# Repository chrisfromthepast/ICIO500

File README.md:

# ICIO500

Transformerless line-in and line-out prototyping platform for the **API VPR-500** 500-series modular rack (`1.500" × 5.250"`), powered by a Daisy Seed DSP carrier card, a vertical rotary-encoder daughtercard, and a modular **0.8 mm Satellite PCB + Swappable Front Panel** faceplate stackup.

---

## Quick Start: View the Full 3D Module in KiCad
1. Open either full 3D assembly in KiCad 10 PCB Editor:
   - **Walnut / Stained Wood Horizontal Slots + Diffuser Film:** [`kicad/icio500_satellite_wood_3d.kicad_pcb`](kicad/icio500_satellite_wood_3d.kicad_pcb)
   - **Dead-Front Smoked Acrylic:** [`kicad/icio500_satellite_acrylic_3d.kicad_pcb`](kicad/icio500_satellite_acrylic_3d.kicad_pcb)
2. Press **`Alt + 3`** to orbit the full stackup (`Carrier PCB` + `Encoder Daughtercard` + inset `0.8 mm Satellite PCB` + `Front Panel` + `Capstan Knob`).
3. Browse pre-rendered views directly in [`renders/`](renders/).

---

## Repository Structure

| Folder | Contents |
| :--- | :--- |
| [`kicad/`](kicad/) | Active KiCad PCBs, schematics (`october_surprise.kicad_sch` + `october_surprise.kicad_pcb`), local footprint libraries (`Cards.pretty/`, `custom.pretty/`), `spice_models/`, `3d_models/`, and 3D assemblies. |
| [`fabrication/`](fabrication/) | Ready-to-upload manufacturing packages separated into `in_production/` (locked) and `satellite_faceplate/` (active). |
| [`firmware/`](firmware/) | Daisy Seed C++ DSP projects (`roomove/`, `cloudseed/`, `daisyverb/`, `covol/`, `funbox_reverbs/`) and shared pinout header `common/icio500_hw.h`. |
| [`scripts/`](scripts/) | Python CAD, KiCad schematic/PCB builder, in-KiCad `ngspice` verification, BOM export, DRC, and fab-export scripts. |
| [`renders/`](renders/) | Verified high-resolution KiCad 3D renders of the modular satellite assemblies and rear PCB layout. |
| [`docs/`](docs/) | API VPR-500 mechanical spec (`api_vpr_500_spec.pdf`), raw manufacturer PDFs (`datasheets/`), `october_surprise_schematic.pdf`, draft BOM, and `ngspice` verification plots. |
| [`archive/`](archive/) | Archived Rev-1 carrier reference (`archive/rev1_bad_carrier/`), preserved strictly as mechanical salvage reference. |

---

## Board & Fabrication Status

| Subsystem | Design Files | Manufacturing Package | Status |
| :--- | :--- | :--- | :--- |
| **VPR-500 Carrier PCB (`October Surprise` Rev 2)** | `kicad/october_surprise.kicad_sch`, `kicad/october_surprise.kicad_pcb` | *(Pre-routing — Subcircuit #1 `POWER` verified)* | **IN DESIGN (Schematic-First + In-KiCad `ngspice`)** |
| **Encoder Daughtercard** | `kicad/encoder_board.kicad_pcb` | [`fabrication/in_production/jlcpcb_encoder/`](fabrication/in_production/jlcpcb_encoder/) | **IN PRODUCTION (Locked)** |
| **Capstan Vernier Knob** | [`scripts/generate_capstan_v2_knob.py`](scripts/generate_capstan_v2_knob.py) | [`fabrication/in_production/jlc3dp_knob_v2/`](fabrication/in_production/jlc3dp_knob_v2/) | **IN PRODUCTION (Locked)** |
| **0.8 mm Satellite Active PCB** | `kicad/faceplate_satellite.kicad_pcb`, `kicad/faceplate_logic.kicad_sch` | [`fabrication/satellite_faceplate/jlcpcb_satellite_pcb/`](fabrication/satellite_faceplate/jlcpcb_satellite_pcb/) | **ACTIVE (0.8 mm 2L FR4, Matte Black)** |
| **Swappable Front Panels** | [`scripts/generate_sendcutsend_faceplates.py`](scripts/generate_sendcutsend_faceplates.py) | [`fabrication/satellite_faceplate/sendcutsend_panels/`](fabrication/satellite_faceplate/sendcutsend_panels/) | **ACTIVE (SendCutSend/Ponoko DXFs + STEP + Preview)** |

---

## Modular Satellite Stackup Notes
- **Hidden Satellite Inset:** `faceplate_satellite.kicad_pcb` (`35.10 × 113.35 mm`, `0.8 mm` 2-layer FR4, recommend **Matte Black** soldermask) sits inset `1.50 mm` left/right and `10.00 mm` top/bottom behind the `38.10 × 133.35 mm` front panel so only the single-layer wood/acrylic panel meets the 500-series rack rails.
- **No Blind Slots Required:** Reverse-mount gull-wing LEDs (`D1..D16`) mount on `B.Cu` over standard `1.92 × 1.68 mm` full NPTH oval slots.
- **Front Panel Diffuser Options:**
  - *Horizontal-Slot Wood (`0.125"` / `3.175 mm`):* `10×` `7.20 × 2.40 mm` horizontal stadium slots (`8.00 mm` pitch) + `6× Ø2.40 mm` knob-ring ports, backed by a flat sheet of translucent milky-white diffusion tape/film (e.g., `3M 3635-70` or Roscolux Tough Frost) sandwiched between the Satellite PCB and Wood.
  - *Dead-Front Smoked Acrylic (`0.118"` / `3.000 mm`):* Zero LED cutouts — all `16` LEDs shine directly through the translucent smoked panel.
- **Mechanical Mating:** `BR1/BR2` (`WP-SMRA-M3`), `J1` (`2x10` header), top `2× M2.5` screws, and the `PEC11R` `M7` bushing mate directly with the locked Carrier and Encoder PCBs. With `3.00–3.18 mm` front panels, place a `~1.8–2.0 mm` spacer inside the in-production Capstan Knob bore to maintain the `1.00 mm` click clearance.

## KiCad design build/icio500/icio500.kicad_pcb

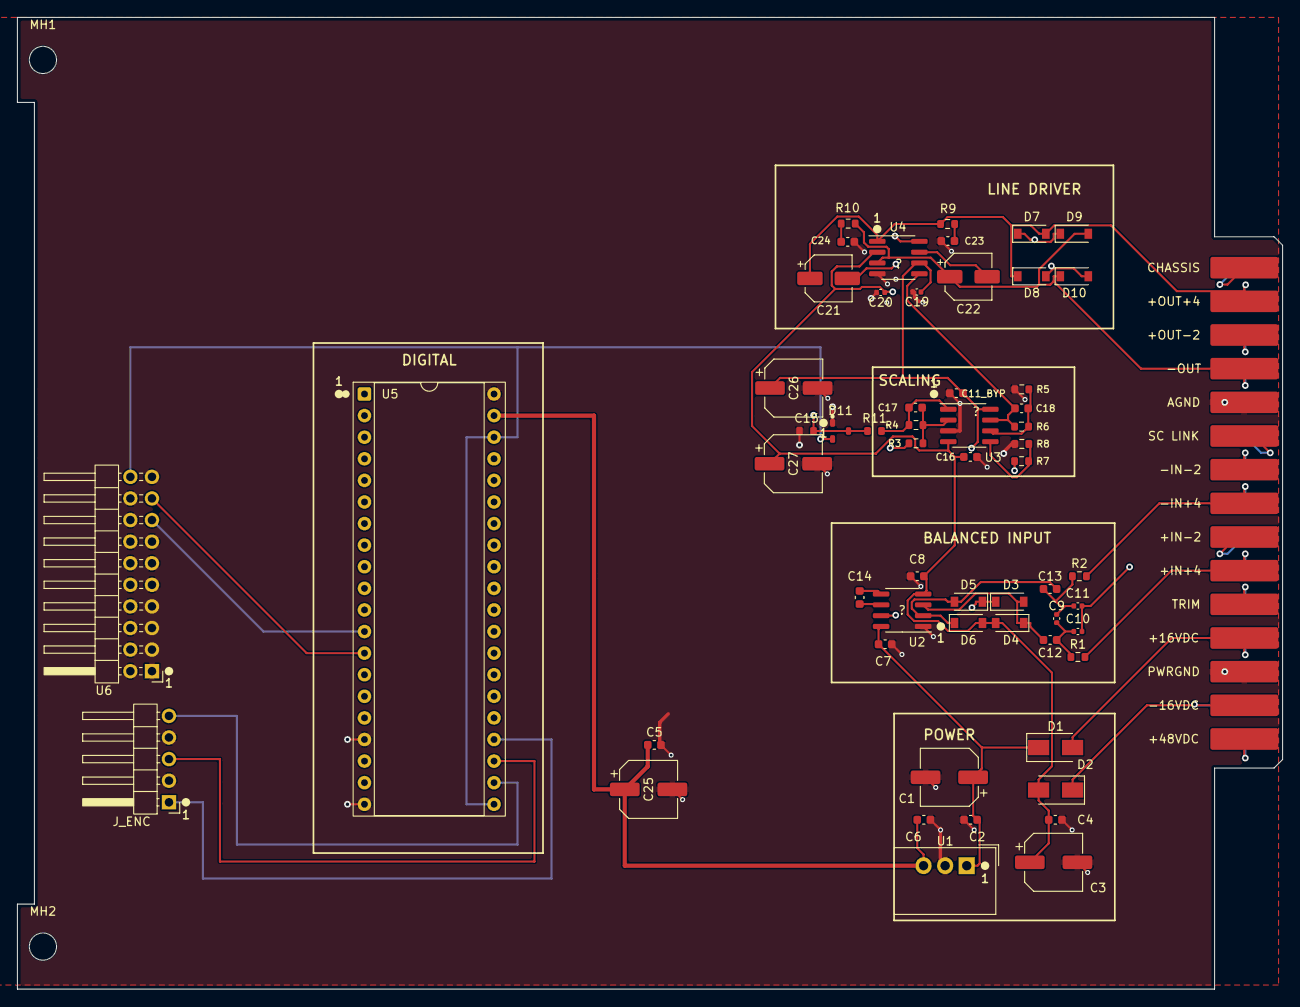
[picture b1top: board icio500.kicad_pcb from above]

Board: 4 copper layers, 148.8 x 114.3 mm, 60 parts (0 on the bottom side), 35 nets.

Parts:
C1, C3, C25, C26, C27: ?; CP_Elec_6.3x5.4
C2, C4, C5, C6, C7, C8, C11_BYP, C12, C13, C14, C16, C17, C18, C23, C24: C0603
C9, C10, C11, C19, C20: C0402
C15: 100pF; C0603
C21, C22: ?; CP_Elec_5x5.4
D1, D2: ?; D_SMA
D3, D4, D5, D6, D7, D8, D9, D10: ?; D_SOD-123
D11: BAT54S; SOT-23
J1: ?; EDA_306
J_ENC: Conn_01x05_Encoder; PinHeader_1x05_P2.54mm_Horizontal
MH1, MH2: MountingHole_3.2mm_M3
R1, R2, R3, R4, R5, R6, R7, R8, R9, R10: R0603
R11: 1k; R0603
U1: TSR 1-2450; Converter_DCDC_TRACO_TSR-1_THT
U2, U3, U4: ?; SOIC-8_3.9x4.9mm_P1.27mm
U5: ?; DIP-40_W15.24mm_Socket
U6: 2541WR-2x10P; PinHeader_2x10_P2.54mm_Horizontal

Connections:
+3.3V: D11.2, U5.21, U5.38, U6.20
audio_in_from_daisy_plus: R7.1, U5.18
audio_out: R3.1, U2.7
audio_out_to_1646: C18.1, R6.1, U3.7, U4.5
chassis_gnd: C10.2, C11.2, J1.1
cm: C14.1, U2.6
d14: J_ENC.5, U5.22
daisy_5v_power: C5.1, C6.1, C25.1, U1.3, U5.39
daisy_audio_in: C15.1, D11.3, R11.2, U5.16
driver.r_zobel_minus-vcc: C24.1, R10.2
driver.r_zobel_plus-vcc: C23.1, R9.2
gnd: C1.2, C2.2, C3.2, C4.2, C5.2, C6.2, C7.2, C8.2, C11_BYP.2, C15.2, C16.2, C19.2, C20.2, C23.2, C24.2, C25.2, C26.2, C27.2, D11.1, J1.5, J1.13, J_ENC.2, J_ENC.4, R5.1, R8.1, U1.2, U2.1, U3.3, U4.4, U5.17, U5.20, U5.40, U6.1, U6.2, U6.3, U6.4, U6.5, U6.6, U6.7, U6.8, U6.9, U6.10, U6.11, U6.12, U6.13, U6.14, U6.16, U6.18, U6.19
gpio_enc_b: J_ENC.3, U5.23
gpio_enc_sw: J_ENC.1, U5.24
i2c1_scl: U5.12, U6.15
i2c1_sda: U5.13, U6.17
in_minus: C13.2, D5.2, D6.1, U2.2
in_minus_1: C17.2, R3.2, R4.2, U3.2
in_minus_2: C18.2, R5.2, R6.2, U3.6
in_minus_4dbu: J1.8, R2.1
in_plus: C12.2, D3.2, D4.1, U2.3
in_plus_2: R7.2, R8.2, U3.5
in_plus_4dbu: J1.10, R1.1
out_minus: C22.1, D9.2, D10.1, J1.4, R10.1, U4.3
out_plus_4dbu: C21.1, D7.2, D8.1, J1.2, R9.1, U4.1
receiver.r_rf_minus-vcc: C9.2, C11.1, C13.1, R2.2
receiver.r_rf_plus-vcc: C9.1, C10.1, C12.1, R1.2
sense_minus: C22.2, U4.7
sense_plus: C21.2, U4.8
sm: C14.2, U2.5
tl072_out1_raw: C17.1, R4.1, R11.1, U3.1
v_minus: C3.1, C4.1, C8.1, C16.1, C20.1, C27.1, D2.2, D4.2, D6.2, D8.2, D10.2, U2.4, U3.4, U4.2
v_minus_16v: D2.1, J1.14
v_plus: C1.1, C2.1, C7.1, C11_BYP.1, C19.1, C26.1, D1.1, D3.1, D5.1, D7.1, D9.1, U1.1, U2.8, U3.8, U4.6
v_plus_16v: D1.2, J1.12

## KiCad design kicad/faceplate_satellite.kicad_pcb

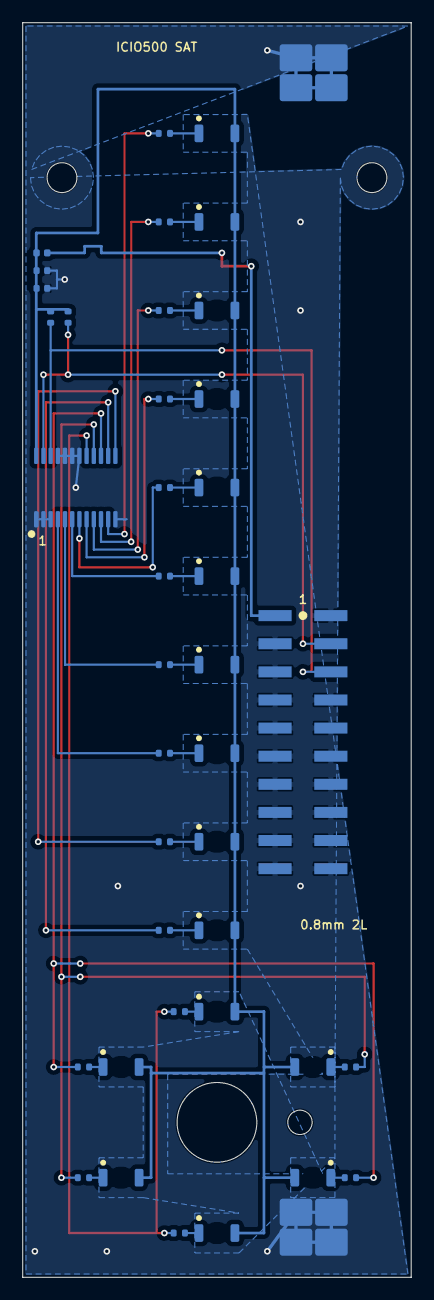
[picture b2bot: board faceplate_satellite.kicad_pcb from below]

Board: 2 copper layers, 35.1 x 113.3 mm, 43 parts (41 on the bottom side), 34 nets.

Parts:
BR1, BR2: WP-SMRA-M3; Mounting_Wuerth_WP-SMRA-M3_L7mm_7466303_Horizontal
C1: 100nF; C_0402_1005Metric
C2: 10uF; C_0402_1005Metric
D1, D2, D3, D4, D5, D6, D7, D8, D9, D10, D11, D12, D13, D14, D15, D16: LED_1206_3216Metric_ReverseMount_Hole1.8x2.4mm
FB1: BLM15AX601SN1D; L_0402_1005Metric
J1: Conn_02x10_Odd_Even; PinSocket_2x10_P2.54mm_Vertical_SMD
MH_TOP_L: MountingHole_2.7mm_M2.5
MH_TOP_R: MountingHole_2.7mm_M2.5
R1: 68R; R_0402_1005Metric
R2, R3: 82R; R_0402_1005Metric
R4, R5, R6, R7, R8, R9, R10, R16, R17, R18, R19, R20, R21: 100R; R_0402_1005Metric
R11, R12: 4.7k; R_0402_1005Metric
U1: PCA9555PW; TSSOP-24_4.4x7.8mm_P0.65mm

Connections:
+3V3: C1.1, C2.1, D1.2, D2.2, D3.2, D4.2, D5.2, D6.2, D7.2, D8.2, D9.2, D10.2, D11.2, D12.2, D13.2, D14.2, D15.2, D16.2, FB1.1, R11.1, R12.1, U1.24
+3V3_IN: FB1.2, J1.2
GND: BR1.1, BR2.1, C1.2, C2.2, J1.1, J1.4, J1.6, J1.7, J1.8, J1.9, J1.10, J1.11, J1.12, J1.13, J1.14, J1.15, J1.16, J1.17, J1.18, J1.19, J1.20, U1.1, U1.2, U1.3, U1.12, U1.18, U1.19, U1.20, U1.21
LED_1: R1.2, U1.11
LED_2: R2.2, U1.10
LED_3: R3.2, U1.9
LED_4: R4.2, U1.8
LED_5: R5.2, U1.7
LED_6: R6.2, U1.6
LED_7: R7.2, U1.5
LED_8: R8.2, U1.4
LED_9: R9.2, U1.13
LED_10: R10.2, U1.14
unnamed: D1.1, R1.1
unnamed: D2.1, R2.1
unnamed: D3.1, R3.1
unnamed: D4.1, R4.1
unnamed: D5.1, R5.1
unnamed: D6.1, R6.1
unnamed: D7.1, R7.1
unnamed: D8.1, R8.1
unnamed: D9.1, R9.1
unnamed: D10.1, R10.1
unnamed: D11.1, R16.2
unnamed: D12.1, R17.2
unnamed: D13.1, R18.2
unnamed: D14.1, R19.2
unnamed: D15.1, R20.2
unnamed: D16.1, R21.2
RGB_B: R18.1, R21.1, U1.16
RGB_G: R17.1, R20.1, U1.15
RGB_R: R16.1, R19.1, U1.17
SCL: J1.5, R12.2, U1.22
SDA: J1.3, R11.2, U1.23

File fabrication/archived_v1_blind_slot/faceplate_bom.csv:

Comment,Designator,Footprint,LCSC Part #
WP-SMRA-M3,"BR1,BR2",Mounting_Wuerth_WP-SMRA-M3_L7mm_7466303_Horizontal,C5523891
100nF,C1,C_0402_1005Metric,C1525
10uF,C2,C_0402_1005Metric,C15525
BLM15AX601SN1D,FB1,L_0402_1005Metric,C76886
Conn_02x10_Odd_Even,J1,PinSocket_2x10_P2.54mm_Vertical_SMD,C41427539
68R,R1,R_0402_1005Metric,C25131
82R,"R2,R3",R_0402_1005Metric,C25136
100R,"R4,R5,R6,R7,R8,R9,R10,R16,R17,R18,R19,R20,R21",R_0402_1005Metric,C25076
4.7k,R11,R_0402_1005Metric,C25900
4.7k,R12,R_0805_2012Metric,C17673
0R,"R13,R14,R15,R22,R23,R24,R25",R_0805_2012Metric,C17414
PCA9555PW,U1,TSSOP-24_4.4x7.8mm_P0.65mm,C128392
XL-3216SURC-FB,"D1,D11,D14",LED_1206_3216Metric_ReverseMount_Hole1.8x2.4mm,C3646938
XL-3216UYC-FB,"D2,D3",LED_1206_3216Metric_ReverseMount_Hole1.8x2.4mm,C3646939
XL-3216UGC-FB,"D4,D5,D6,D7,D8,D9,D10,D12,D15",LED_1206_3216Metric_ReverseMount_Hole1.8x2.4mm,C3646937
XL-3216UBC-FB,"D13,D16",LED_1206_3216Metric_ReverseMount_Hole1.8x2.4mm,C3646941

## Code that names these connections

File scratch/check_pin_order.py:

# Let's check U6 pins and U5 pins to see if they can connect on F.Cu without crossings:
# U6 has two rows:
# Left row (X = 53.46):
#   Pin 20: p20 (Y=97.61)
#   Pin 18: p18 (Y=100.16)
#   Pin 16: gpio_disp_dc (Y=102.69)
#   Pin 14: spi1_sck (Y=105.23)
#   Pin 12: spi1_mosi (Y=107.77)
#   Pin 10: gpio_enc_b (Y=110.31)
#   Pin 8 : d13 (Y=112.85)
#   Pin 6 : i2c1_scl (Y=115.39)
#   Pin 4 : i2c1_sda (Y=117.93)
#   Pin 2 : audio_in_r (Y=120.47)
#
# Right row (X = 56.00):
#   Pin 19: p19 (Y=97.61)
#   Pin 17: gpio_disp_res (Y=100.16)
#   Pin 15: spi1_cs (Y=102.69)
#   Pin 13: spi1_miso (Y=105.23)
#   Pin 11: gpio_enc_sw (Y=107.77)
#   Pin 9 : d14 (Y=110.31)
#   Pin 7 : gnd (Y=112.85)
#   Pin 5 : gnd (Y=115.39)
#   Pin 3 : gnd (Y=117.93)
#   Pin 1 : daisy_5v_power (Y=120.47)

# Now on U5 (with rot = 0):
# Row 1 (X = X_u5, facing U6):
#   Pin 1 : gpio_disp_res (ly = 0.00)
#   Pin 6 : gpio_disp_dc  (ly = 12.70)
#   Pin 7 : spi1_cs       (ly = 15.24)
#   Pin 8 : spi1_sck      (ly = 17.78)
#   Pin 9 : spi1_miso     (ly = 20.32)
#   Pin 10: spi1_mosi     (ly = 22.86)
#   Pin 11: i2c1_scl      (ly = 25.40)
#   Pin 12: i2c1_sda      (ly = 27.94)
#   Pin 13: d13           (ly = 30.48)
#   Pin 16: d14           (ly = 38.10)
#   Pin 17: gpio_enc_b    (ly = 40.64)
#   Pin 18: gpio_enc_sw   (ly = 43.18)

# Notice: On U6, pins alternate between Right row (X=56) and Left row (X=53.46)!
# Can the Right row of U6 exit directly to the right (+X) towards U5?
# YES! The right row is at X=56, so nothing is to the right of it!
# Can the Left row of U6 exit?
# Left row is at X=53.46. It can exit between the pins of the Right row, OR exit to the left, or on another layer (like B.Cu or In1.Cu)!
# Wait, can we use 2 layers: F.Cu for one row, B.Cu for the other row?
# Through-hole pins exist on ALL copper layers!
# Since U6 and U5 are through-hole, you can route directly on F.Cu AND B.Cu with ZERO vias!
print("Through-hole pins connect directly on F.Cu and B.Cu without ANY vias!")

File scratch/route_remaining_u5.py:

from grid_router import GridRouter
from test_autoroute import simplify_path

# True U5 pin positions on Row 2 (X = 110.24):
# Pin 35: (110.24, 90.0 + 12.70) = (110.24, 102.70) -> audio_in_from_daisy_plus -> R7 pin 1 (172.30, 97.90)
# Pin 37: (110.24, 90.0 + 7.62)  = (110.24, 97.62)  -> daisy_audio_in           -> C17 pin 1 (159.825, 91.60)
# Pin 39: (110.24, 90.0 + 2.54)  = (110.24, 92.54)  -> daisy_5v_power           -> C25 pin 1 (128.42, 136.51)

rem_router = GridRouter(x_min=90.0, x_max=180.0, y_min=70.0, y_max=155.0, step=0.5)

# Block other pins
# Route daisy_audio_in on layer 0 (F.Cu)
path_audio_in = rem_router.route_net((110.24, 97.62), (159.825, 91.60), layer=0, clearance=0.4)
if path_audio_in:
    s_audio_in = simplify_path(path_audio_in)
    print(f"SUCCESS: daisy_audio_in routed with {len(s_audio_in)} points")
else:
    print("FAILED daisy_audio_in")

# Route daisy_5v_power from (110.24, 92.54) to (128.42, 136.51) on layer 0 (F.Cu)
path_pwr = rem_router.route_net((110.24, 92.54), (128.42, 136.51), layer=0, clearance=0.6)
if path_pwr:
    s_pwr = simplify_path(path_pwr)
    print(f"SUCCESS: daisy_5v_power routed with {len(s_pwr)} points")
else:
    print("FAILED daisy_5v_power")

# Route audio_in_from_daisy_plus on layer 1 (B.Cu) from (110.24, 102.70) to (172.30, 97.90)
path_plus = rem_router.route_net((110.24, 102.70), (172.30, 97.90), layer=1, clearance=0.4)
if path_plus:
    s_plus = simplify_path(path_plus)
    print(f"SUCCESS: audio_in_from_daisy_plus routed with {len(s_plus)} points")
else:
    print("FAILED audio_in_from_daisy_plus")

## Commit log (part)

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2026-06-04 Initial plan
2026-06-04 Add atopile That1200Stage module with project configuration
    - Create ato.yaml with generics dependency for component resolution
    - Add elec/src/that1200_stage.ato with That1200 input stage module
    - Fix connection operators (-> to ~) for bidirectional passive nets
    - Split declarations onto separate lines for reliable parsing
    - Update .gitignore for atopile build artifacts
2026-06-04 Create That1646 stage with capacitor and resistor setup
    Define That1646 component and its connections.
2026-06-04 Add level shifter component with active scaling
2026-06-04 Add isolated DC-DC converter and power supply module
2026-06-04 Add VprEdgeConnector component with pinout definition
2026-06-04 Create VprCarrier500 module with hardware connections
2026-06-04 expand to daisy using atopile
2026-06-04 atopile
2026-06-04 good start
2026-06-04 Implement Roomove DSP firmware port with GPIO toggles for pink noise and hard bypass
2026-06-04 Improve firmware code quality by defining magic numbers as named constants
2026-06-05 preliminary layout
2026-06-05 Fix stereo output handling in AudioCallback
2026-06-05 Add missing RoomoveDSP header dependency
2026-06-05 Clarify RoomoveDSP clamp parameter naming
2026-06-05 Remove unused RoomoveDSP.h file
2026-06-05 Refactor main.cpp to inherit from Roomove
2026-06-05 autoroute
2026-06-08 added daisy
2026-06-09 getting closer!
2026-06-10 alotta antigravity and trying to help
2026-06-10 clean up repository: move scripts to folder and untrack .venv
2026-06-10 Track KiCad files in build output
2026-06-13 getting closer for daisy seed
2026-06-13 pretty ok layout for daisy
    antigravity
2026-06-14 closer still but weird
2026-06-14 1600 looks good
2026-06-14 input loks pretty ok
2026-06-14 better still
2026-06-16 closer than ever
2026-06-16 clanker got it close
2026-06-16 clanker doing better
2026-06-18 daisy close to good
2026-06-18 add faceplate
2026-06-21 Fix faceplate ato build errors, proper THAT1646 electrolytic caps, and restore pristine faceplate.kicad_pcb
2026-06-21 starting hand routing
2026-06-21 nudged things into a shape I like
2026-06-21 footprints are getting closer to correct
2026-06-21 footprints and placement getting closer
2026-06-22 hand placement almost finished
2026-06-22 placement by human complete
2026-06-22 autorouted on top of human layout
2026-06-27 many revisions maybe not better facepate
